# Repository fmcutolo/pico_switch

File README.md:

## Table of Contents
- [Issues](#issues)
- [Datasheets](#datasheets)
  - [Pico](#pico)
  - [RYLR998 LoRa Module](#rylr998-lora-module)
  - [RTC/EEPROM Module](#rtceeprom-module)
  - [Misc](#misc)

# Issues
9/19/26  

I discovered that the last change in the file pico_switch.pro was not checked in. I can't remember why that change is there and what it does, except that it contains more info and settings. From what I learned online, chatgpt, is that *.pro file does not affect schematic or pcbnew. 
When this change occurred, there was an issue with the allpcb fabricator regarding whole-to-whole spacing which was resolved. I'm not sure if this change related to that, the two files below shows the details of that. I'm including these files here just in case I may need th

[allpcb hole-to-hole spacing issue](images/issues_from_all_pcb.pdf)

[hole-to-hole affected area](images/allpcb_issue.jpg)

# Datasheets

## Pico

| Component | Part Number | Datasheet |
|-----------|-------------|-----------|
| Microcontroller | Pico   | [Pico Datasheet](datasheets/raspberry_pi_picos/pico-datasheet.pdf) |
| Microcontroller | Pico | [python sdk](datasheets/raspberry_pi_picos/RPI-PICO-R3-PUBLIC-SCHEMATIC.pdf) |
| Microcontroller | Pico | [Pico Pinout](datasheets/raspberry_pi_picos/Pico-R3-A4-Pinout.pdf) |
| Microcontroller | Pico2   | [Pico2 Datasheet](datasheets/raspberry_pi_picos/pico-2-datasheet.pdf) |
| Microcontroller | Pico2w   | [Pico2w Datasheet](datasheets/raspberry_pi_picos/pico-2-w-datasheet.pdf) |
| Microcontroller | Pico2w   | [Pico2w Schematic](datasheets/raspberry_pi_picos/pico-2-w-schematic.pdf) |
| Microcontroller | RP2040 | [RP2040 Datasheet](datasheets/raspberry_pi_picos/rp2040-datasheet.pdf) |
| Microcontroller | RP2350 | [RP2350 Datasheet](datasheets/raspberry_pi_picos/rp2350-datasheet.pdf) |
| Microcontroller | PicoX | [python sdk](datasheets/raspberry_pi_picos/raspberry-pi-pico-python-sdk.pdf) |
| Microcontroller | Info   | [Connecting Pico to the internet](datasheets/raspberry_pi_picos/connecting-to-the-internet-with-pico-w.pdf) |
| Microcontroller | Info | [Hardware design with RP2350](datasheets/raspberry_pi_picos/hardware-design-with-rp2350.pdf) |

## RYLR998 LoRa Module
| Component | Part Number | Datasheet |
|-----------|-------------|-----------|
| RF Transceiver | RYLR998    | [RYLR998 datasheet](datasheets/RYLR998/RYLR998.pdf) |
| RF Transceiver | RYLR998 | [RYLR998 AT Commands](datasheets/RYLR998/RYLR998_AT_Commands.pdf) |

## RTC/EEPROM Module
| Component | Part Number | Datasheet |
|-----------|-------------|-----------|
| RTC       | DS3231          | [DS3231 datasheet](datasheets/DS3231_AT24C32_Module/DS3231.pdf) |
| EEPROM    | AT24C32         | [AT24C32](datasheets/DS3231_AT24C32_Module/RYLR998_AT_Commands.pdf) |

## Misc
| Component | Part Number | Datasheet |
|-----------|-------------|-----------|
| TX/RX module       | FT232RL          | [FT232RL datasheet](datasheets/FT232RL_USB_TO_TTL.pdf) |
| Ultrasonic sensor       | HC-SR04 user's manual          | [HC-SR04 Users' Manual](datasheets/HC-SR04_user's_manual.pdf) |
| Voltage regulator       | MCP1700-3302E/TO          | [3.3V Low Dropout (LDO) Voltage](datasheets/MCP1700-Data-Sheet-20001826F.pdf) |
| LED       | Color: RGB  | [Common Anode RGB LED](datasheets/RGB_LED.JPG) |

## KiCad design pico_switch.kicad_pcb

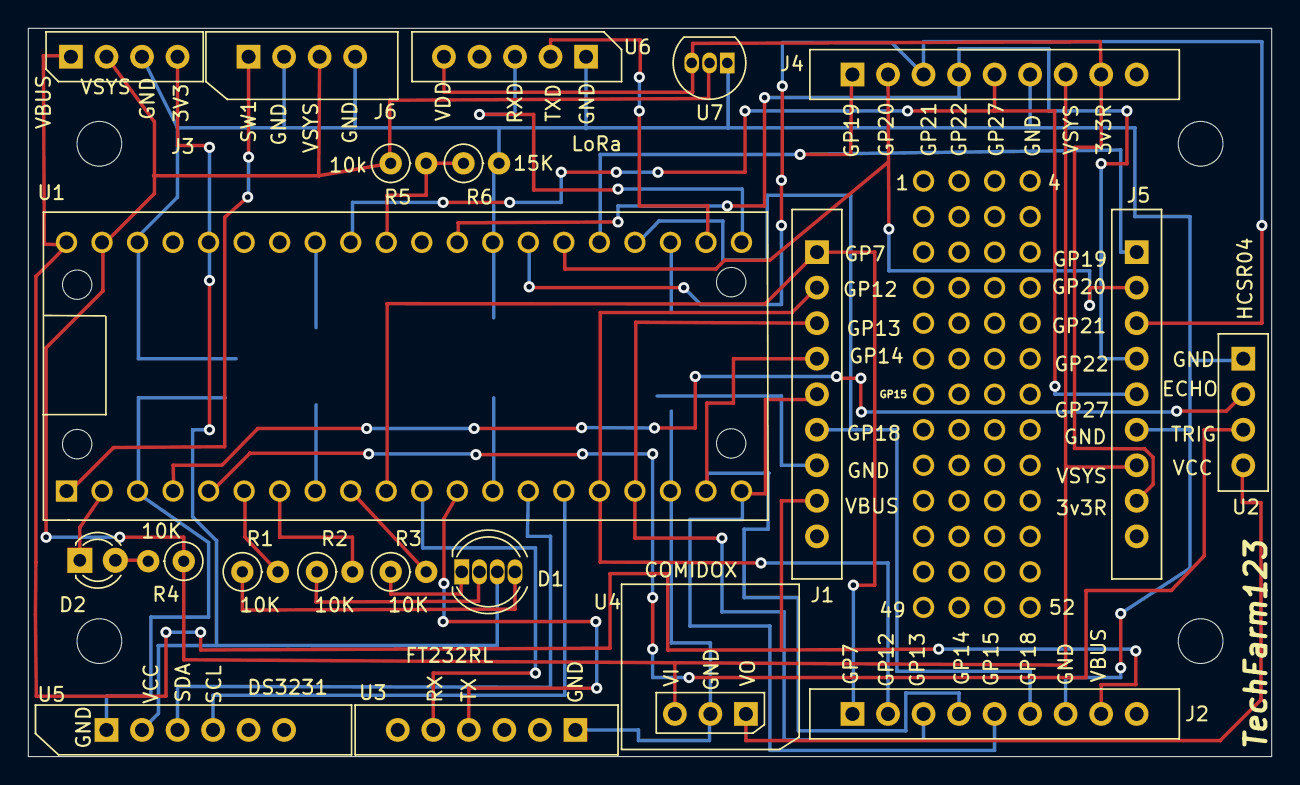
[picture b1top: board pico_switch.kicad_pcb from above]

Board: 2 copper layers, 88.9 x 52.1 mm, 26 parts (0 on the bottom side), 35 nets.

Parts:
D1: LED_BGAR; LED_D5.0mm-4_RGB
D2: LED; LED_D3.0mm
J1, J2, J4, J5: Conn_01x09_Female_pico; on_the_edge_9_pin_2.54mm_pitch
J3: Conn_01x04_Female; on_the_edge_4pin_2.54mm_pitch
J6: Conn_01x04_Female; four_pin_on_the_edge_screw_terminal
MH1, MH2, MH3, MH4: MountingHole_3.2mm_M3
PPADS: proto_pads_4x13_2.54mm
R1, R2, R3, R4: 10K; R_Axial_DIN0207_L6.3mm_D2.5mm_P2.54mm_Vertical
R5: 10k; R_Axial_DIN0207_L6.3mm_D2.5mm_P2.54mm_Vertical
R6: 15K; R_Axial_DIN0207_L6.3mm_D2.5mm_P2.54mm_Vertical
U1: pico
U2: HC_SR04; hc_sr04_on_the_edge
U3: usb_to_ttl; six_pin_on_the_edge
U4: step_up_5v; step_up_5v_fp
U5: ds3231; six_pin_on_the_edge_21_4
U6: LoRa; rylr998
U7: MCP1700-3302E_TO92; TO-92_Inline

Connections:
3V3: D1.3, J3.4, U1.36, U5.2
GND: J1.7, J2.7, J3.3, J4.6, J5.6, J6.2, J6.4, R6.2, U1.3, U1.8, U1.13, U1.18, U1.23, U1.28, U1.33, U1.38, U2.1, U3.1, U4.2, U5.1, U6.1, U7.1
unnamed: D1.1, R3.1
unnamed: D1.2, R2.1
unnamed: D1.4, R1.1
unnamed: D2.1, U1.2
unnamed: D2.2, R4.2
unnamed: J1.1, J2.1, U1.10
unnamed: J1.2, J2.2, U1.16
unnamed: J1.3, J2.3, U1.17
unnamed: J1.4, J2.4, U1.19
unnamed: J1.5, J2.5, U1.20
unnamed: J1.6, J2.6, U1.24
unnamed: J4.1, J5.1, U1.25
unnamed: J4.2, J5.2, U1.26
unnamed: J4.3, J5.3, U1.27
unnamed: J4.4, J5.4, U1.29
unnamed: J4.5, J5.5, U1.32
unnamed: J4.8, J5.8, U6.5, U7.3
unnamed: J6.1, U1.1
unnamed: R1.2, U1.6
unnamed: R2.2, U1.7
unnamed: R3.2, U1.9
unnamed: R5.2, R6.1, U1.31
unnamed: U1.4, U2.2
unnamed: U1.5, U2.3
unnamed: U1.11, U3.5
unnamed: U1.12, U3.4
unnamed: U1.14, U5.3
unnamed: U1.15, U5.4
unnamed: U1.21, U6.3
unnamed: U1.22, U6.2
unnamed: U2.4, U4.1
VBUS: J1.8, J2.8, J3.1, U1.40
VSYS: J3.2, J4.7, J5.7, J6.3, R4.1, R5.1, U1.39, U4.3, U7.2

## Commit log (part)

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2026-01-08 First pico pcb!
2026-01-16 PCB fixes/cleanup and getting it ready for AllPCP fabrication
2026-01-17 trace/vias tweaking for spacing mostly
